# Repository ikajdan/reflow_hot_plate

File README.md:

<h1 align="center">
  
  <br><br>
  Reflow Hot Plate
  <br><br>
</h1>

<p align="center">
  <a href="#features">Features</a> •
  <a href="#hardware">Hardware</a> •
  <a href="#firmware">Firmware</a> •
  <a href="#usage">Usage</a> •
  <a href="#gallery">Gallery</a> •
  <a href="#license">License</a>
</p>

The STM32-Based Reflow Hot Plate Project is an open-source initiative aimed at creating a reflow soldering hot plate using the STM32 microcontroller. This project provides an affordable and customizable solution for hobbyists looking to solder surface-mount components onto printed circuit boards with precision and control.

## Features

- **Precise temperature control:** The STM32 microcontroller provides accurate temperature control, ensuring optimal soldering results for a wide range of solder pastes and components.
- **User-friendly interface:** A user-friendly interface, featuring an OLED display and tactile buttons, allows you to easily set and monitor reflow profiles.
- **Customizable reflow profiles:** Create, edit, and save reflow profiles tailored to your specific soldering requirements.
- **Safety mechanisms:** Built-in safety features, such as over-temperature protection and emergency shut-off, ensure a secure soldering environment.
- **Open-source:** The entire project, including schematics, PCB layouts, and firmware is open-source and available for improvement and customization.

## Hardware

The electronic hardware is designed using KiCad. It includes the following components:

- STM32 microcontroller (STM32F103 series)
- N-Channel Power MOSFET for controlling the heating element
- Thermocouple and PT100 sensor for temperature measurement
- OLED display for real-time temperature and soldering progress information
- Buttons for user interaction
- USB-C connector for communication
- Power supply circuitry

The mechanical hardware is designed using FreeCAD. It includes the following components:

- Front panel mask
- Front panel brackets
- Gooseneck mounting

These components are designed to be 3D printed and assembled together to create a complete device.

For detailed hardware schematics, PCB layout and CAD models, please refer to the [Hardware](hardware/) directory.

## Firmware

The firmware for the reflow hot plate is developed using the STM32CubeIDE. It includes:

- Temperature control algorithm
- User interface logic
- Reflow profile management
- Safety and emergency handling

The Cube project can be found in the [Firmware](firmware/) directory.

## Usage

1. Power on the reflow hot plate and wait for it to initialize.
1. Place your PCB with solder paste and components onto the hot plate.
1. Use the tactile buttons and OLED display to navigate through the user interface and select a reflow profile.
1. The hot plate will execute the selected reflow profile, precisely controlling the temperature to solder the components onto the PCB.
1. Once the reflow process is complete, allow the PCB to cool before removing it from the hot plate.

## Gallery

</img>
</img>
</img>
</img>
</img>
</img>

## License

This project is licensed under the [MIT License](LICENSE.md), which means you are free to use, modify, and distribute the project's source code and documentation for both commercial and non-commercial purposes.

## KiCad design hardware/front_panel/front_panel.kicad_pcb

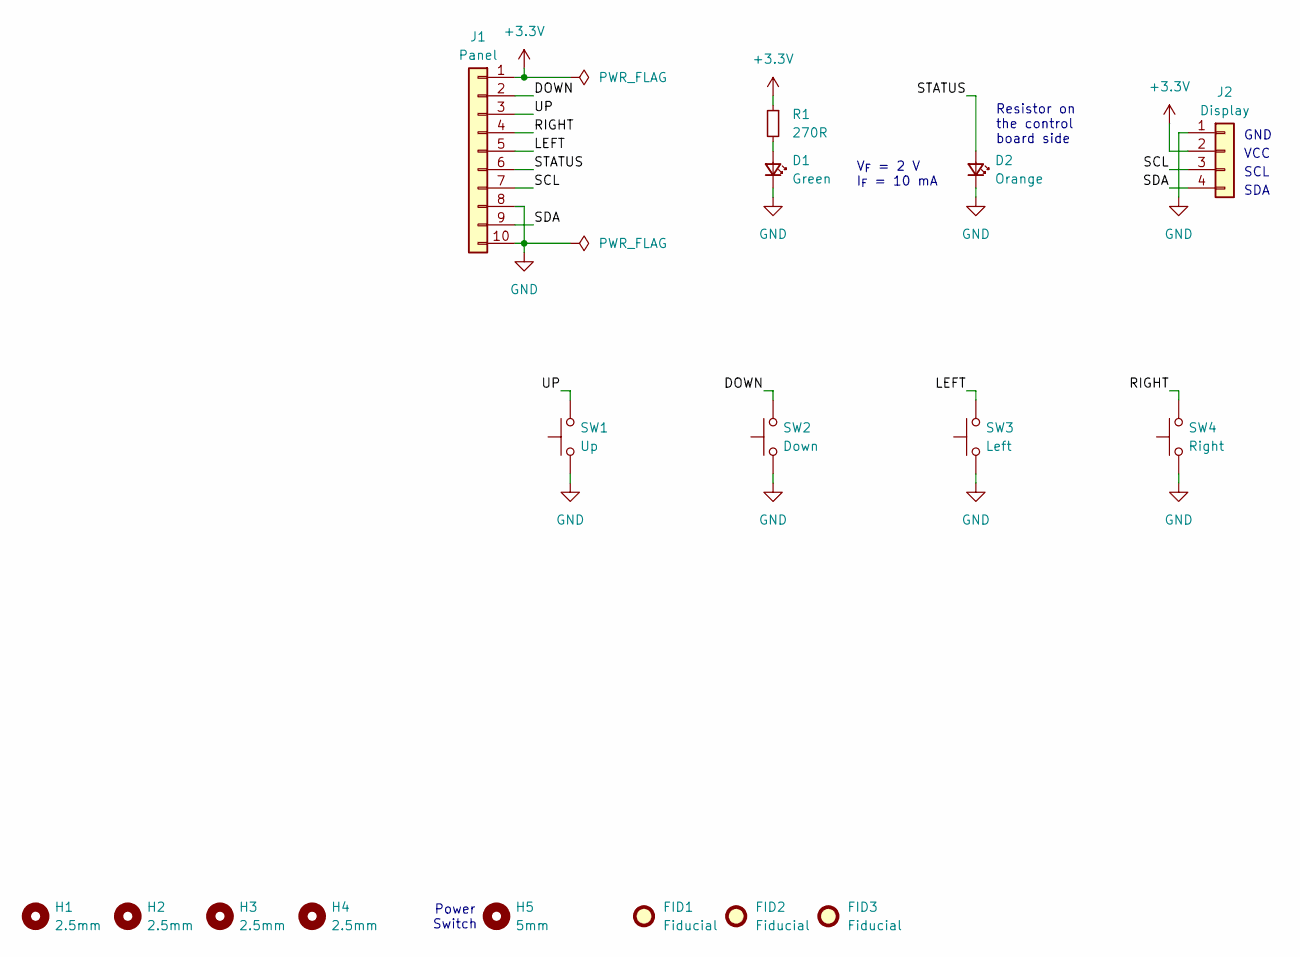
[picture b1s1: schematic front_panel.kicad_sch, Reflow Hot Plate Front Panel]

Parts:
D1: Green; LED_D3.0mm_FlatTop
D2: Orange; LED_D3.0mm_FlatTop
FID1, FID2, FID3: Fiducial; Fiducial_1mm_Mask2mm
H1, H2, H3, H4: 2.5mm; MountingHole_2.5mm
H5: 5mm; MountingHole_5mm
J1: Panel; 52808-1070
J2: Display; 0.96_OLED
R1: 270R; R_0603_1608Metric
SW1: Up; SW_PUSH_6mm_H7.3mm
SW2: Down; SW_PUSH_6mm_H7.3mm
SW3: Left; SW_PUSH_6mm_H7.3mm
SW4: Right; SW_PUSH_6mm_H7.3mm

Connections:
+3.3V: J1.1, J2.2, R1.1
/DOWN: J1.2, SW2.2
/LEFT: J1.5, SW3.2
/RIGHT: J1.4, SW4.2
/SCL: J1.7, J2.3
/SDA: J1.9, J2.4
/STATUS: D2.2 (A), J1.6
/UP: J1.3, SW1.2
GND: D1.1 (K), D2.1 (K), J1.8, J1.10, J2.1, SW1.1, SW2.1, SW3.1, SW4.1
unnamed: D1.2 (A), R1.2

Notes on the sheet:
Resistor on the control board side
Power Switch
SCL
GND
SDA
VCC
V_{F} = 2 V I_{F} = 10 mA

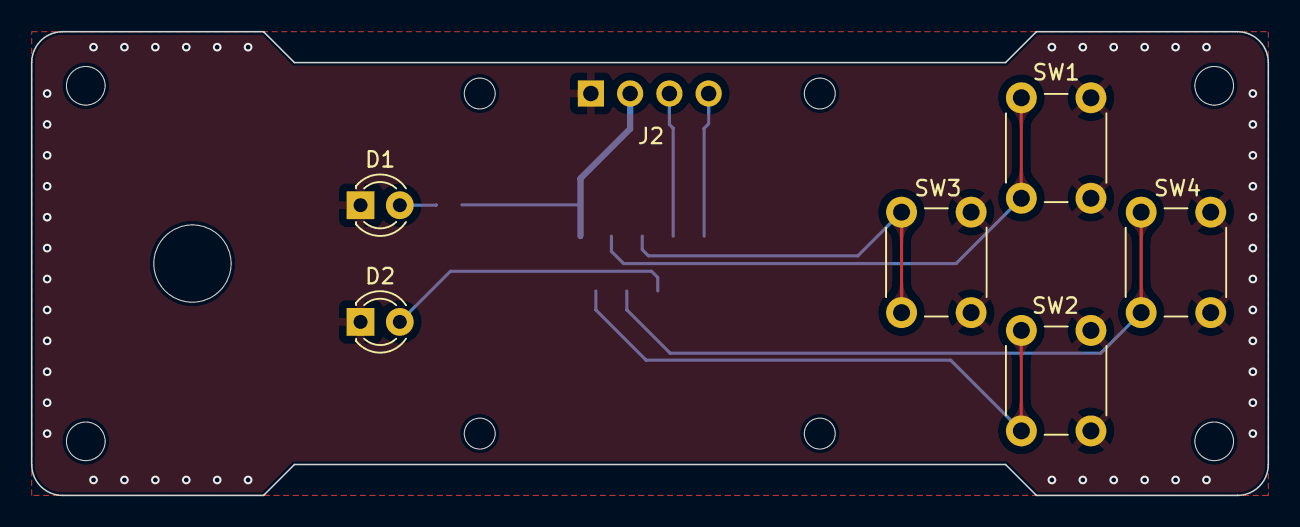
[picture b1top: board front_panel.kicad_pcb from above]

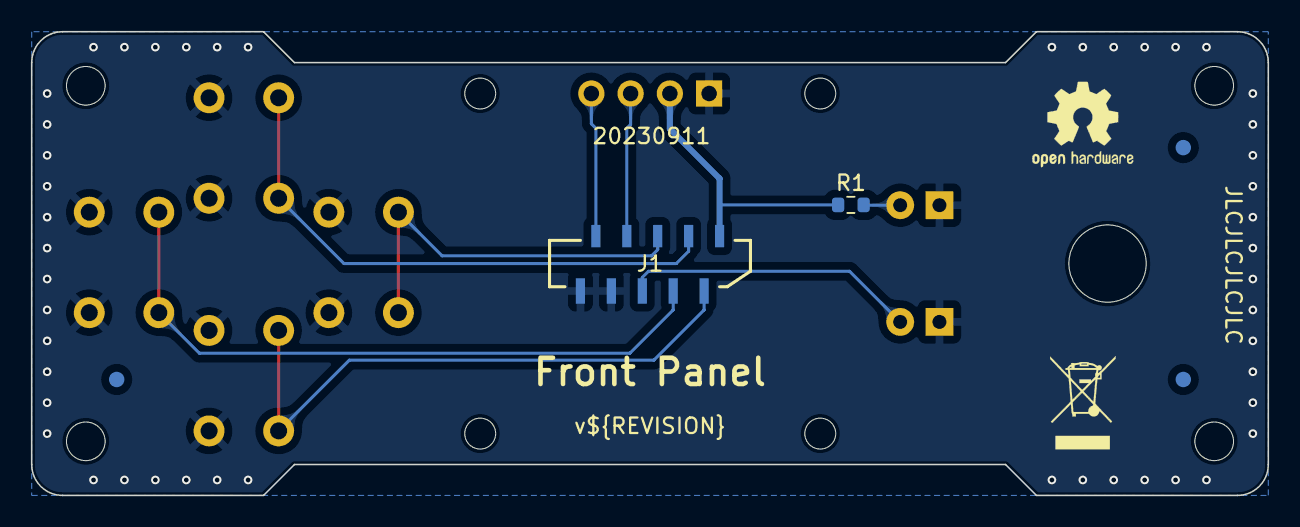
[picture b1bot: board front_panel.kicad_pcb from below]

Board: 2 copper layers, 80.0 x 30.0 mm, 17 parts (5 on the bottom side), 10 nets.

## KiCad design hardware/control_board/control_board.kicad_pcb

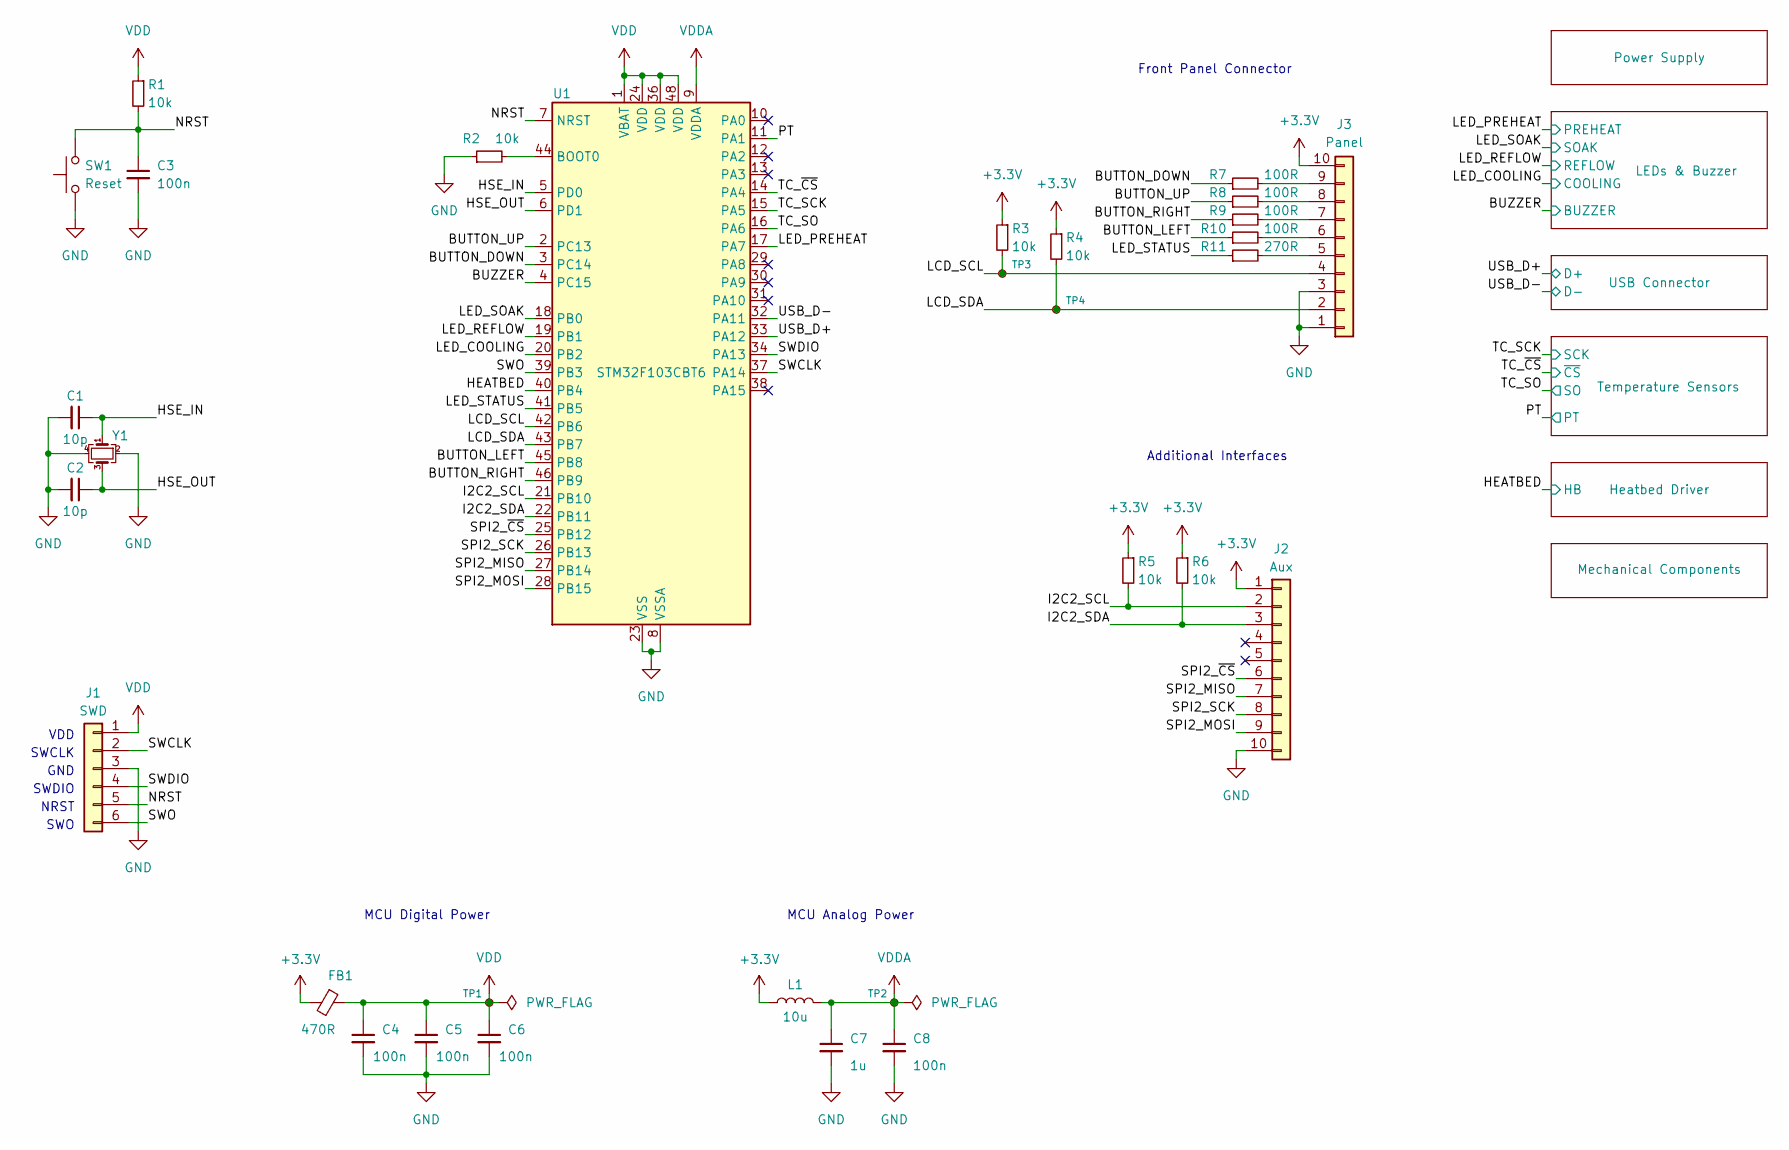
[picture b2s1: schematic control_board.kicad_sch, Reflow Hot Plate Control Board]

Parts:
C1, C2: 10p; C_0603_1608Metric
C3, C4, C5, C6, C8: 100n; C_0603_1608Metric
C7: 1u; C_0603_1608Metric
FB1: 470R; L_0603_1608Metric
J1: SWD; PinHeader_1x06_P2.54mm_Vertical
J2: Aux; PinHeader_2x05_P2.54mm_Vertical
J3: Panel; 52808-1070
L1: 10u; L_0603_1608Metric
R1, R2, R3, R4, R5, R6: 10k; R_0603_1608Metric
R7, R8, R9, R10: 100R; R_0603_1608Metric
R11: 270R; R_0603_1608Metric
SW1: Reset; SW_SPST_B3U-1000P
TP1, TP2, TP3, TP4: TestPoint_Small; TestPoint_Pad_D1.0mm
U1: STM32F103CBT6; LQFP-48_7x7mm_P0.5mm
Y1: 8MHz; Crystal_SMD_3225-4Pin_3.2x2.5mm

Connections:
+3.3V: FB1.2, J2.1, J3.10, L1.1, R3.1, R4.1, R5.1, R6.1; also elsewhere on the board
/BUTTON_DOWN: R7.1, U1.3 (PC14)
/BUTTON_LEFT: R10.1, U1.45 (PB8)
/BUTTON_RIGHT: R9.1, U1.46 (PB9)
/BUTTON_UP: R8.1, U1.2 (PC13)
/BUZZER: U1.4 (PC15); also elsewhere on the board
/HEATBED: U1.40 (PB4); also elsewhere on the board
/HSE_IN: C1.1, U1.5 (PD0), Y1.1
/HSE_OUT: C2.1, U1.6 (PD1), Y1.3
/I2C2_SCL: J2.2, R5.2, U1.21 (PB10)
/I2C2_SDA: J2.3, R6.2, U1.22 (PB11)
/LCD_SCL: J3.4, R3.2, TP3.1, U1.42 (PB6)
/LCD_SDA: J3.2, R4.2, TP4.1, U1.43 (PB7)
/LED_COOLING: U1.20 (PB2); also elsewhere on the board
/LED_PREHEAT: U1.17 (PA7); also elsewhere on the board
/LED_REFLOW: U1.19 (PB1); also elsewhere on the board
/LED_SOAK: U1.18 (PB0); also elsewhere on the board
/LED_STATUS: R11.1, U1.41 (PB5)
/NRST: C3.1, J1.5, R1.2, SW1.2, U1.7 (NRST)
/PT: U1.11 (PA1); also elsewhere on the board
/SPI2_MISO: J2.7, U1.27 (PB14)
/SPI2_MOSI: J2.9, U1.28 (PB15)
/SPI2_SCK: J2.8, U1.26 (PB13)
/SPI2_~CS: J2.6, U1.25 (PB12)
/SWCLK: J1.2, U1.37 (PA14)
/SWDIO: J1.4, U1.34 (PA13)
/SWO: J1.6, U1.39 (PB3)
/TC_SCK: U1.15 (PA5); also elsewhere on the board
/TC_SO: U1.16 (PA6); also elsewhere on the board
/TC_~CS: U1.14 (PA4); also elsewhere on the board
/USB_D+: U1.33 (PA12); also elsewhere on the board
/USB_D-: U1.32 (PA11); also elsewhere on the board
GND: C1.2, C2.2, C3.2, C4.2, C5.2, C6.2, C7.2, C8.2, J1.3, J2.10, J3.1, J3.3, R2.1, SW1.1, U1.8 (VSSA), U1.23 (VSS), U1.35 (VSS), U1.47 (VSS), Y1.2, Y1.4; also elsewhere on the board
unnamed: J3.5, R11.2
unnamed: J3.6, R10.2
unnamed: J3.7, R9.2
unnamed: J3.8, R8.2
unnamed: J3.9, R7.2
unnamed: R2.2, U1.44 (BOOT0)
VDD: C4.1, C5.1, C6.1, FB1.1, J1.1, R1.1, TP1.1, U1.1 (VBAT), U1.24 (VDD), U1.36 (VDD), U1.48 (VDD); also elsewhere on the board
VDDA: C7.1, C8.1, L1.2, TP2.1, U1.9 (VDDA)

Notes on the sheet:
MCU Analog Power
MCU Digital Power
Additional Interfaces
VDD
SWO
SWCLK
Front Panel Connector
SWDIO
NRST
GND

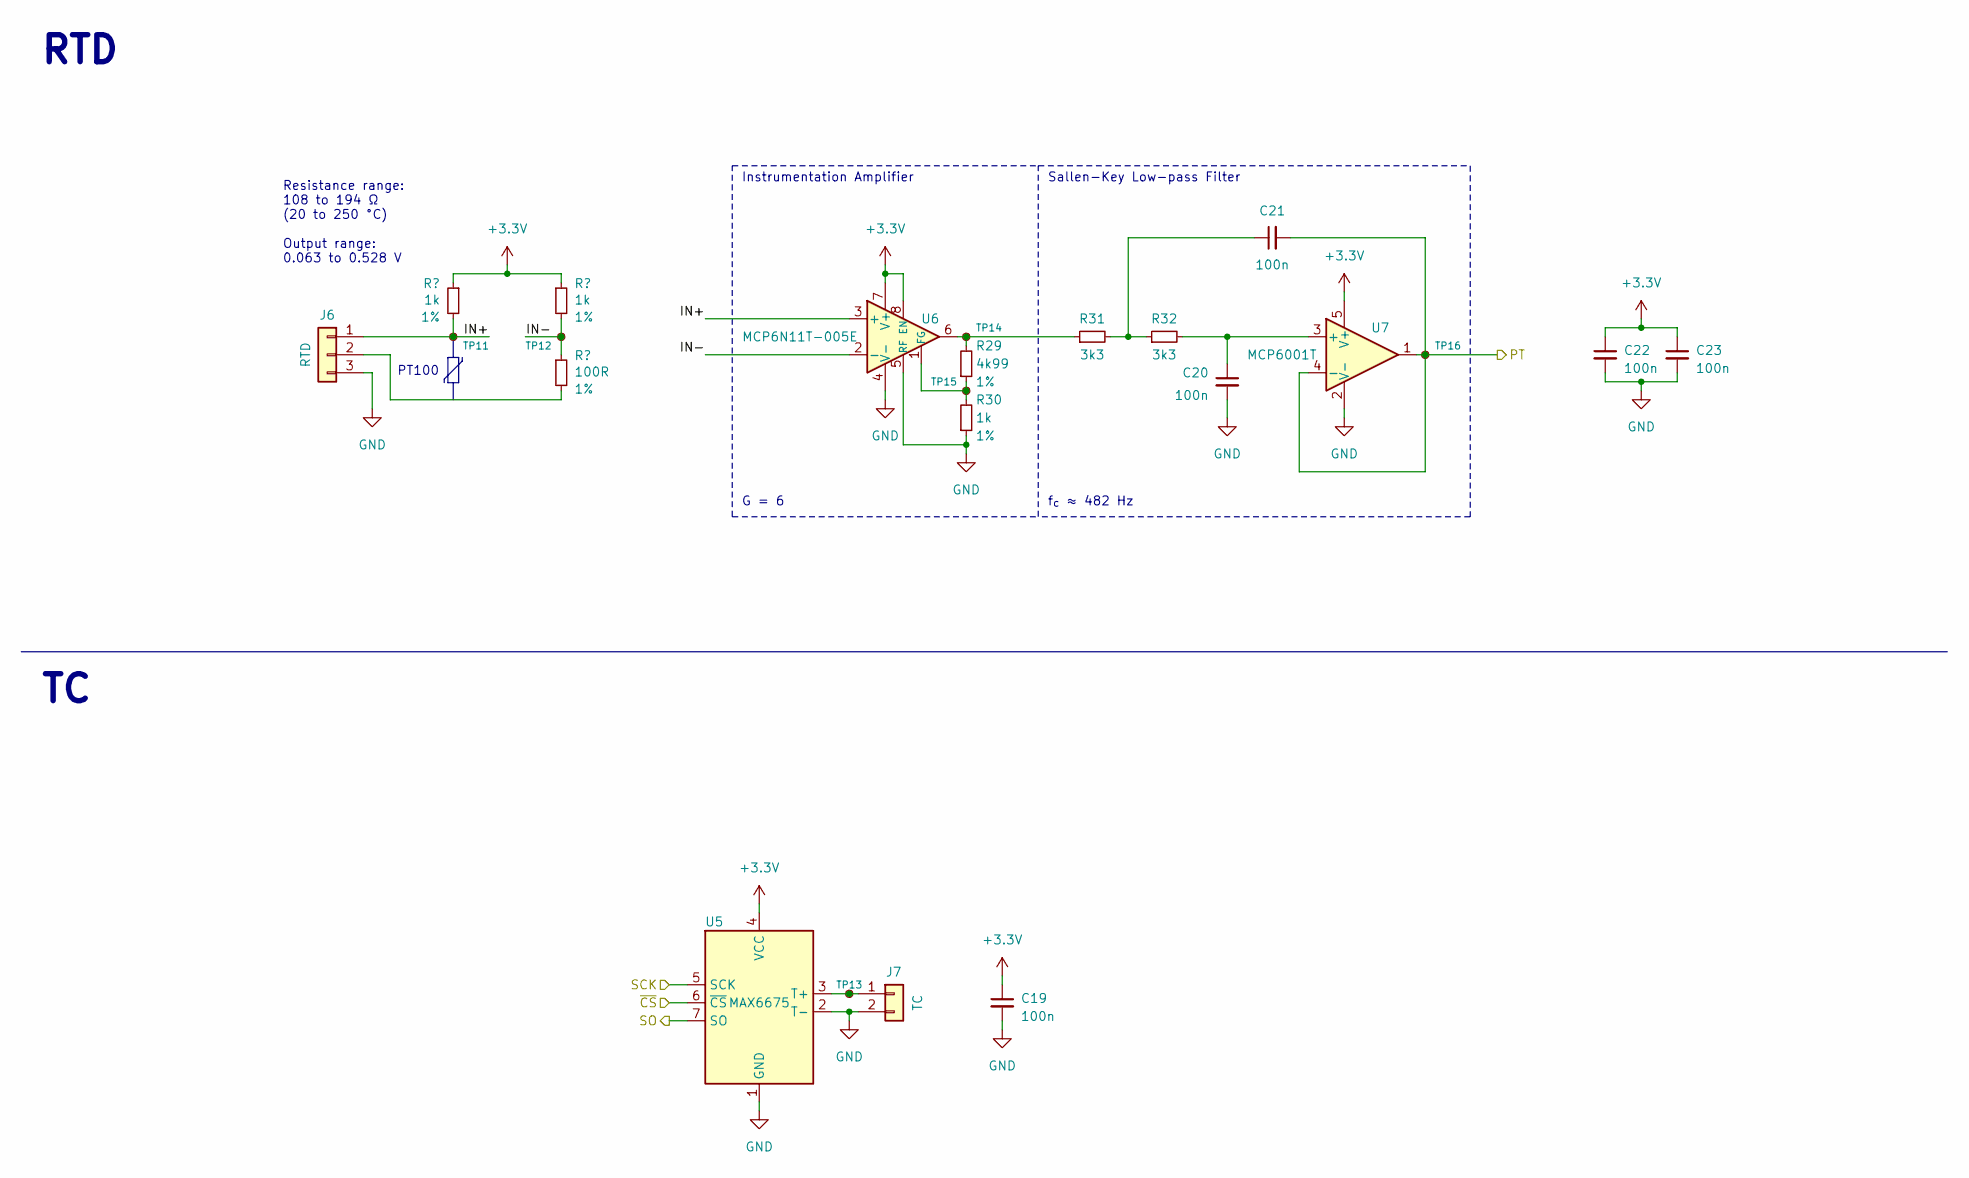
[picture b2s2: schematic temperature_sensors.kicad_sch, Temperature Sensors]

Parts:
C19, C20, C21, C22, C23: 100n; C_0603_1608Metric
J6: RTD; JST_XH_B3B-XH-A_1x03_P2.50mm_Vertical
J7: TC; JST_XH_B2B-XH-A_1x02_P2.50mm_Vertical
R26, R27, R30: 1k; R_0603_1608Metric; Tolerance 1%
R28: 100R; R_0603_1608Metric; Tolerance 1%
R29: 4k99; R_0603_1608Metric; Tolerance 1%
R31, R32: 3k3; R_0603_1608Metric
TP11, TP12, TP13, TP14, TP15, TP16: TestPoint_Small; TestPoint_Pad_D1.0mm
U5: MAX6675; SOIC-8_3.9x4.9mm_P1.27mm
U6: MCP6N11T-005E; SOIC-8_3.9x4.9mm_P1.27mm
U7: MCP6001T; SOT-23-5

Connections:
+3.3V: C19.1, C22.1, C23.1, R26.1, R27.1, U5.4 (VCC), U6.7 (V+), U6.8 (EN), U7.5 (V+); also elsewhere on the board
/PT: C21.2, TP16.1, U7.1, U7.4 (-); also elsewhere on the board
/TC_SCK: U5.5 (SCK); also elsewhere on the board
/TC_SO: U5.7 (SO); also elsewhere on the board
/TC_~CS: U5.6 (~CS); also elsewhere on the board
/Temperature Sensors/IN+: J6.1, R26.2, TP11.1, U6.3 (+)
/Temperature Sensors/IN-: R27.2, R28.1, TP12.1, U6.2 (-)
GND: C19.2, C20.2, C22.2, C23.2, J6.3, J7.2, R30.1, U5.1 (GND), U5.2 (T-), U6.4 (V-), U6.5 (RF), U7.2 (V-); also elsewhere on the board
unnamed: C21.1, R31.2, R32.1
unnamed: J6.2, R28.2
unnamed: J7.1, TP13.1, U5.3 (T+)
unnamed: R29.2, R31.1, TP14.1, U6.6
unnamed: R29.1, R30.2, TP15.1, U6.1 (FG)
unnamed: C20.1, R32.2, U7.3 (+)

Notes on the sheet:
Instrumentation Amplifier
Resistance range: 108 to 194 Ω (20 to 250 °C) Output range: 0.063 to 0.528 V
G = 6
RTD
Sallen-Key Low-pass Filter
f_{c} ≈ 482 Hz
PT100

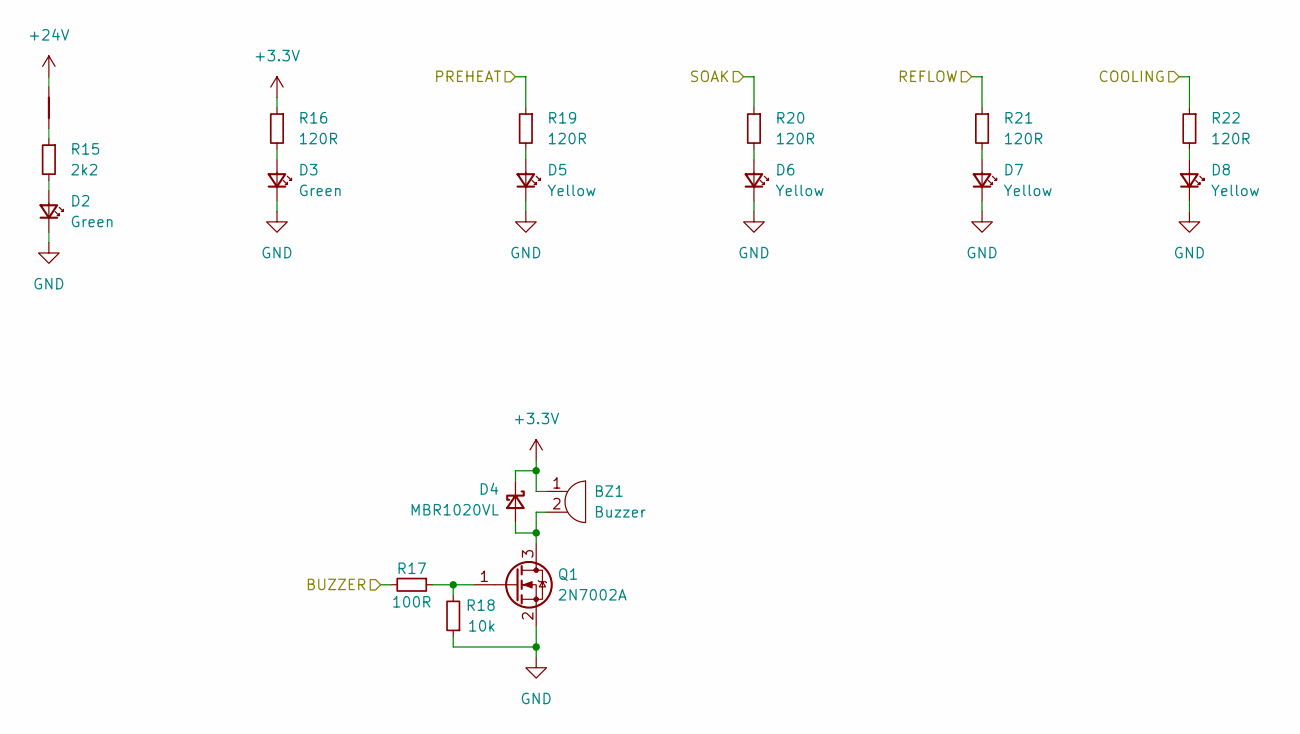
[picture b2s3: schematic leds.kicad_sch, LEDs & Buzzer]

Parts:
BZ1: Buzzer; CMI-9605IC-0380T
D2, D3: Green; LED_0603_1608Metric
D4: MBR1020VL; D_SOD-123F
D5, D6, D7, D8: Yellow; LED_0603_1608Metric
NT1: NetTie_2; NetTie-2_SMD_Pad0.2mm
Q1: 2N7002A; SOT-23
R15: 2k2; R_0603_1608Metric
R16, R19, R20, R21, R22: 120R; R_0603_1608Metric
R17: 100R; R_0603_1608Metric
R18: 10k; R_0603_1608Metric

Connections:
+3.3V: BZ1.1, D4.1 (K), R16.1; also elsewhere on the board
+24V: NT1.2; also elsewhere on the board
/BUZZER: R17.2; also elsewhere on the board
/LED_COOLING: R22.1; also elsewhere on the board
/LED_PREHEAT: R19.1; also elsewhere on the board
/LED_REFLOW: R21.1; also elsewhere on the board
/LED_SOAK: R20.1; also elsewhere on the board
GND: D2.1 (K), D3.1 (K), D5.1 (K), D6.1 (K), D7.1 (K), D8.1 (K), Q1.2 (S), R18.1; also elsewhere on the board
unnamed: D2.2 (A), R15.2
unnamed: D3.2 (A), R16.2
unnamed: BZ1.2, D4.2 (A), Q1.3 (D)
unnamed: D5.2 (A), R19.2
unnamed: D6.2 (A), R20.2
unnamed: D7.2 (A), R21.2
unnamed: D8.2 (A), R22.2
unnamed: NT1.1, R15.1
unnamed: Q1.1 (G), R17.1, R18.2

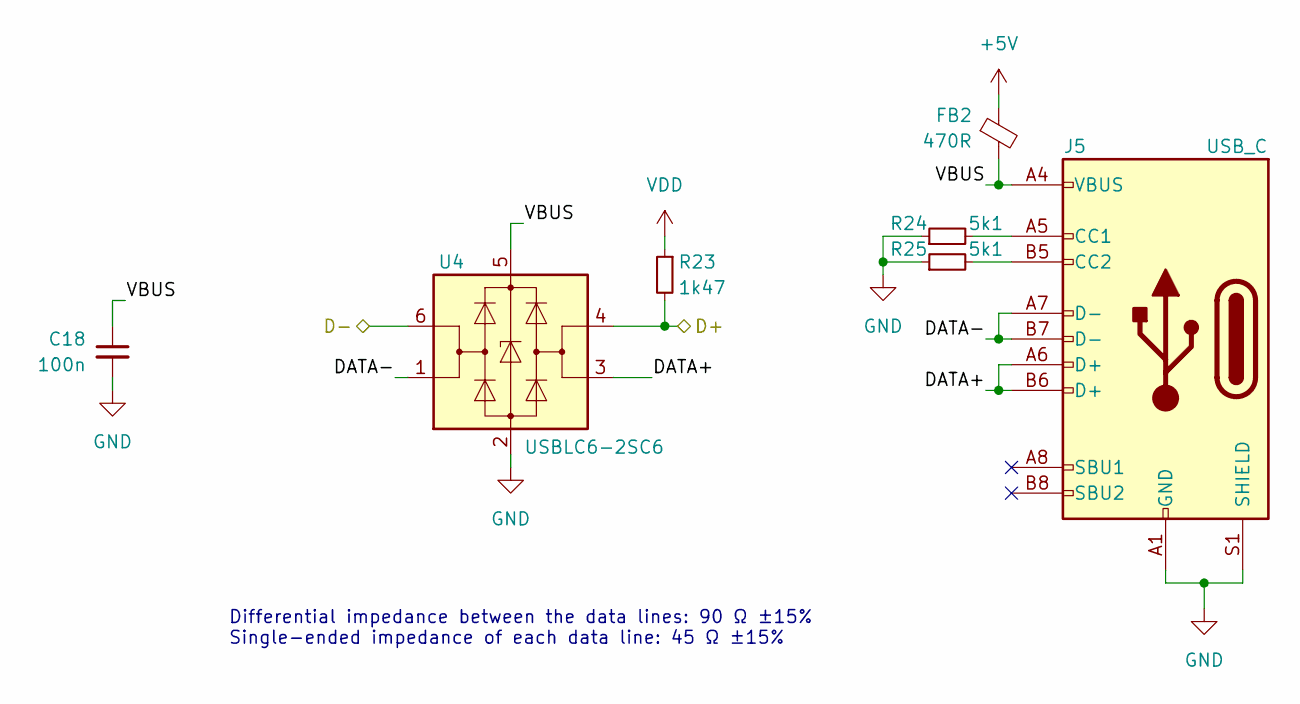
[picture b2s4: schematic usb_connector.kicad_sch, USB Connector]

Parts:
C18: 100n; C_0603_1608Metric
FB2: 470R; L_0603_1608Metric
J5: USB_C; USB4105-GF-A
R23: 1k47; R_0603_1608Metric
R24, R25: 5k1; R_0603_1608Metric
U4: USBLC6-2SC6; SOT-23-6

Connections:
+5V: FB2.1; also elsewhere on the board
/USB Connector/DATA+: J5.A6 (D+), J5.B6 (D+), U4.3 (I/O2)
/USB Connector/DATA-: J5.A7 (D-), J5.B7 (D-), U4.1 (I/O1)
/USB Connector/VBUS: C18.1, FB2.2, J5.A4 (VBUS), J5.A9 (VBUS), J5.B4 (VBUS), J5.B9 (VBUS), U4.5 (VBUS)
/USB_D+: R23.2, U4.4 (I/O2); also elsewhere on the board
/USB_D-: U4.6 (I/O1); also elsewhere on the board
GND: C18.2, J5.A1 (GND), J5.A12 (GND), J5.B1 (GND), J5.B12 (GND), J5.S1 (SHIELD), R24.1, R25.1, U4.2 (GND); also elsewhere on the board
unnamed: J5.A5 (CC1), R24.2
unnamed: J5.B5 (CC2), R25.2
VDD: R23.1; also elsewhere on the board

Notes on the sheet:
Differential impedance between the data lines: 90 Ω ±15% Single-ended impedance of each data line: 45 Ω ±15%

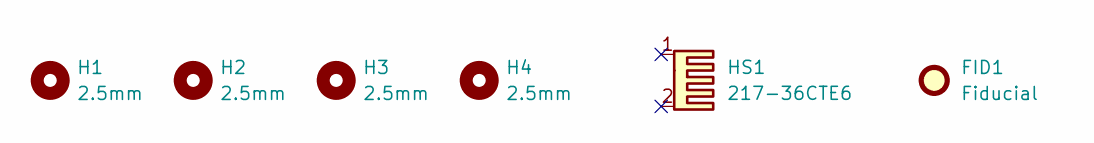
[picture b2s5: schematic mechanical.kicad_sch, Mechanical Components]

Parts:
FID1: Fiducial; Fiducial_1mm_Mask2mm
H1, H2, H3, H4: 2.5mm; MountingHole_2.5mm
HS1: 217-36CTE6; 217-36CTx6

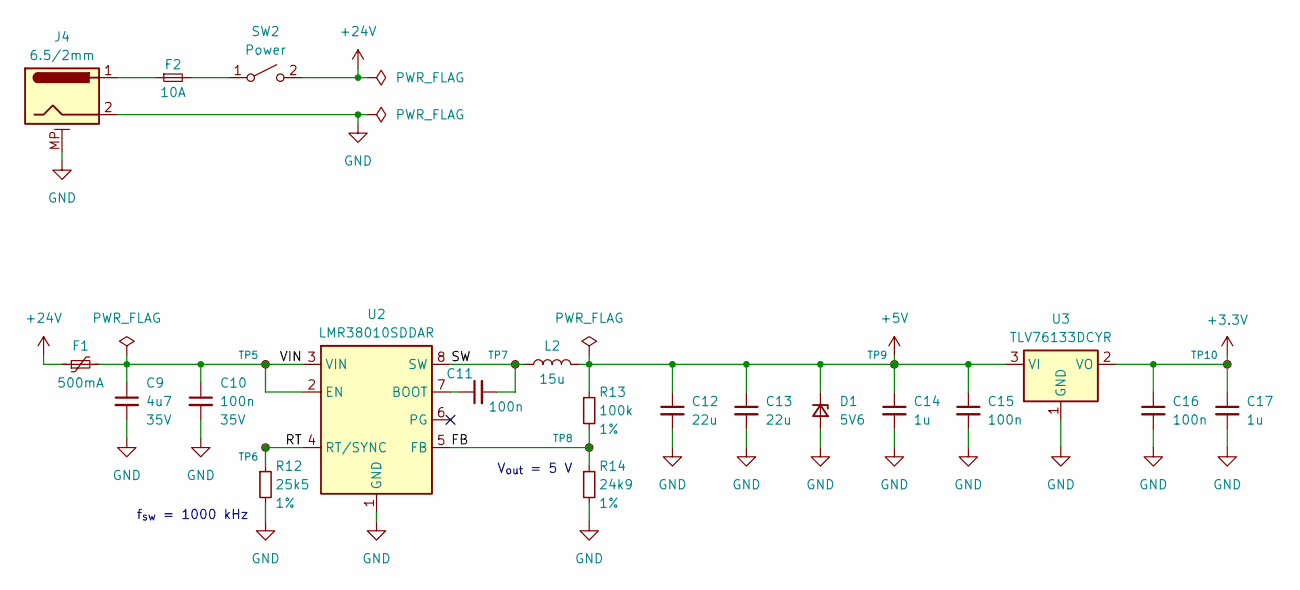
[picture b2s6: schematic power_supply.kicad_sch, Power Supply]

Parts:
C9: 4u7; C_0603_1608Metric; Rated Voltage 35V
C10: 100n; C_0603_1608Metric; Rated Voltage 35V
C11, C15, C16: 100n; C_0603_1608Metric
C12, C13: 22u; C_0603_1608Metric
C14, C17: 1u; C_0603_1608Metric
D1: 5V6; D_SOD-123F
F1: 500mA; MINISMDCx
F2: 10A; Fuseholder_Cylinder-5x20mm_Schurter_0031_8201_Horizontal_Op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
J4: 6.5/2mm; BarrelJack_CUI_PJ-063AH_Horizontal
L2: 15u; SRN6028Cx
R12: 25k5; R_0603_1608Metric; Tolerance 1%
R13: 100k; R_0603_1608Metric; Tolerance 1%
R14: 24k9; R_0603_1608Metric; Tolerance 1%
SW2: Power; SwitchWireRelief
TP5, TP6, TP7, TP8, TP9, TP10: TestPoint_Small; TestPoint_Pad_D1.0mm
U2: LMR38010SDDAR; TI_SO-PowerPAD-8_ThermalVias
U3: TLV76133DCYR; SOT-223-3_TabPin2

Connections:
+3.3V: C16.1, C17.1, TP10.1, U3.2 (VO); also elsewhere on the board
+5V: C12.1, C13.1, C14.1, C15.1, D1.1 (K), L2.2, R13.1, TP9.1, U3.3 (VI); also elsewhere on the board
+24V: F1.1, SW2.2 (B); also elsewhere on the board
/Power Supply/FB: R13.2, R14.1, TP8.1, U2.5 (FB)
/Power Supply/RT: R12.1, TP6.1, U2.4 (RT/SYNC)
/Power Supply/SW: C11.2, L2.1, TP7.1, U2.8 (SW)
/Power Supply/VIN: C9.1, C10.1, F1.2, TP5.1, U2.2 (EN), U2.3 (VIN)
GND: C9.2, C10.2, C12.2, C13.2, C14.2, C15.2, C16.2, C17.2, D1.2 (A), J4.2, J4.MP (MountPin), R12.2, R14.2, U2.1 (GND), U2.9 (EP), U3.1 (GND); also elsewhere on the board
unnamed: F2.1, J4.1
unnamed: F2.2, SW2.1 (A)
unnamed: C11.1, U2.7 (BOOT)

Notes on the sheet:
f_{sw} = 1000 kHz
V_{out} = 5 V

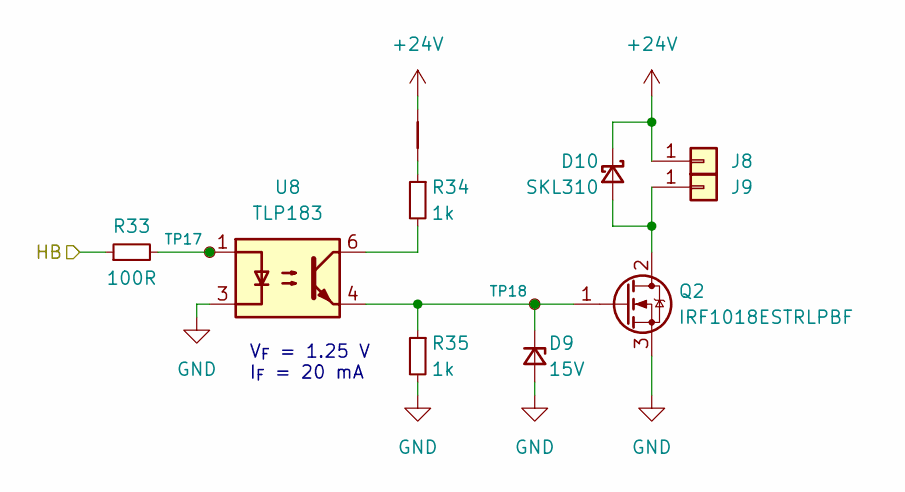
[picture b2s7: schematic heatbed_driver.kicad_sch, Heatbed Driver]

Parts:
D9: 15V; D_SOD-123F
D10: SKL310; D_SOD-123F
J8, J9: Conn_01x01; Pad_D5mm_H2.2mm_Via
NT2: NetTie_2; NetTie-2_SMD_Pad0.2mm
Q2: IRF1018ESTRLPBF; TO-263-2
R33: 100R; R_0603_1608Metric
R34, R35: 1k; R_0603_1608Metric
TP17, TP18: TestPoint_Small; TestPoint_Pad_D1.0mm
U8: TLP183; SOIC-4_4.55x3.7mm_P2.54mm

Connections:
+24V: D10.1 (K), J8.1, NT2.2; also elsewhere on the board
/HEATBED: R33.1; also elsewhere on the board
GND: D9.2 (A), Q2.3 (S), R35.2, U8.3; also elsewhere on the board
unnamed: D9.1 (K), Q2.1 (G), R35.1, TP18.1, U8.4
unnamed: D10.2 (A), J9.1, Q2.2 (D)
unnamed: NT2.1, R34.1
unnamed: R33.2, TP17.1, U8.1
unnamed: R34.2, U8.6

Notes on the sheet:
V_{F} = 1.25 V I_{F} = 20 mA

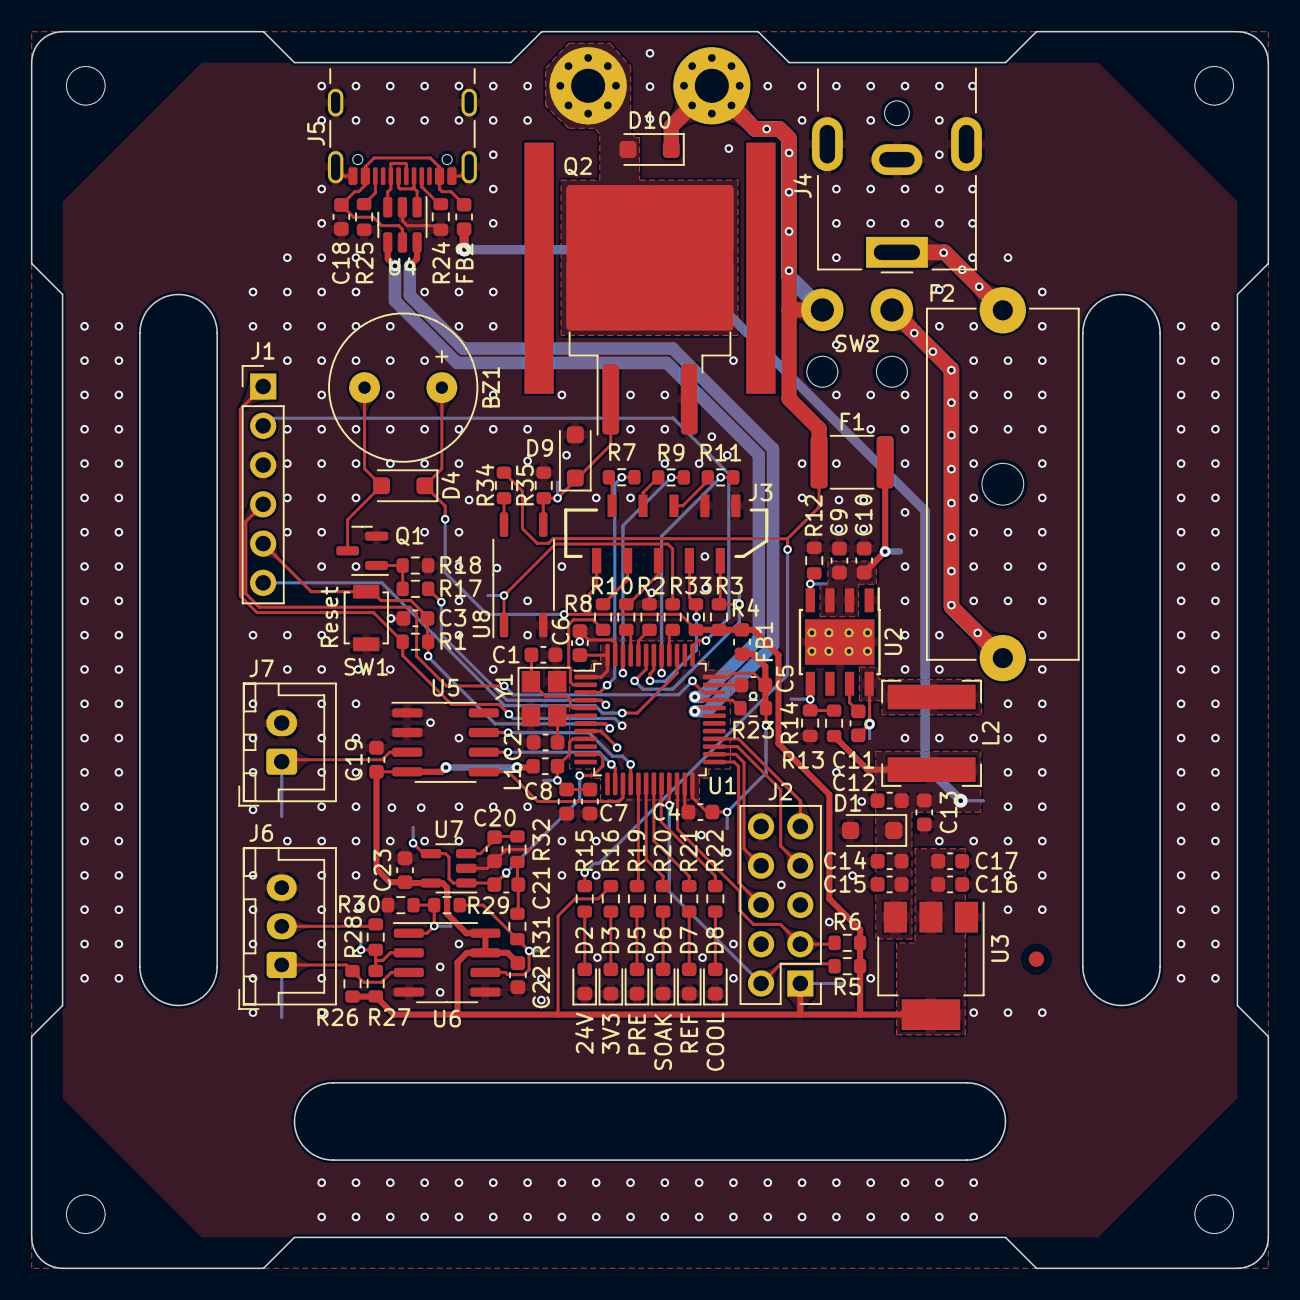
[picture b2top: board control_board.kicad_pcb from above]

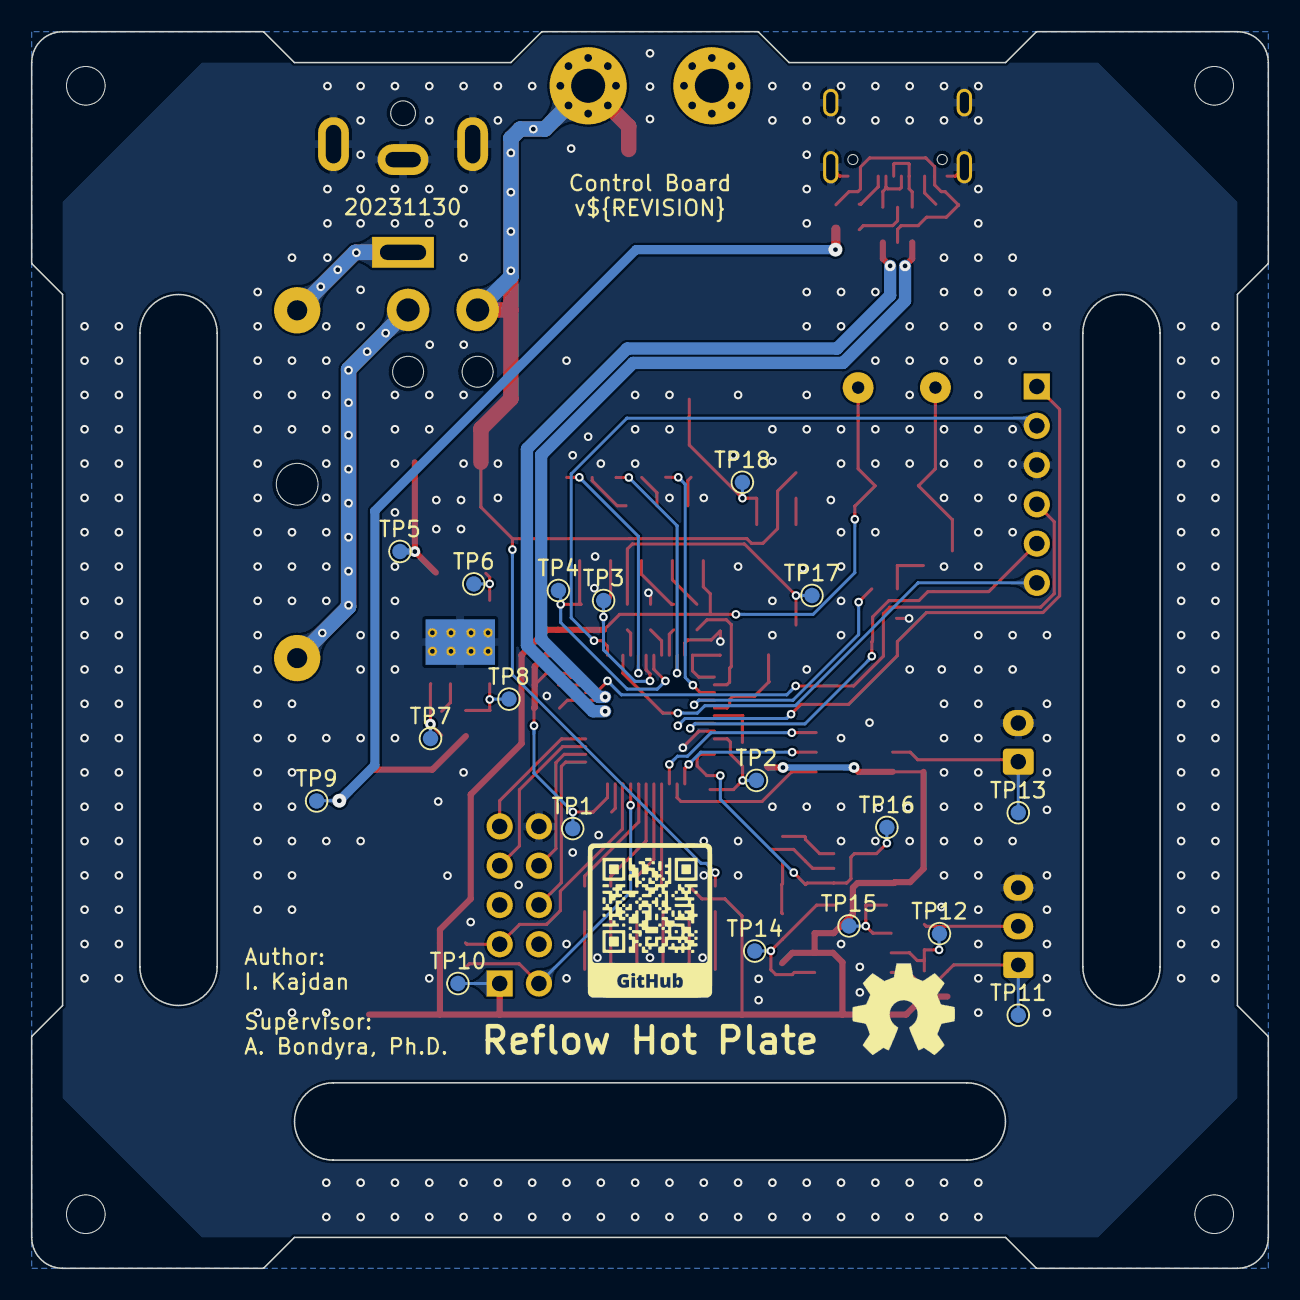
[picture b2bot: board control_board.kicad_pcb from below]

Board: 2 copper layers, 80.0 x 80.0 mm, 123 parts (18 on the bottom side), 77 nets.

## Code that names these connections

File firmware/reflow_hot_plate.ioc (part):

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Mcu.Name=STM32F103C(8-B)Tx
Mcu.Package=LQFP48
Mcu.UserName=STM32F103CBTx
PA1.GPIOParameters=GPIO_Label
PA1.GPIO_Label=PT
PA1.Signal=ADCx_IN1
PA11.GPIOParameters=GPIO_Label
PA11.GPIO_Label=USB_D-
PA11.Mode=Device
PA11.Signal=USB_DM
PA12.GPIOParameters=GPIO_Label
PA12.GPIO_Label=USB_D+
PA12.Mode=Device
PA12.Signal=USB_DP
PA13.GPIOParameters=GPIO_Label
PA13.GPIO_Label=SWDIO
PA13.Mode=Trace_Asynchronous_SW
PA13.Signal=SYS_JTMS-SWDIO
PA14.GPIOParameters=GPIO_Label
PA14.GPIO_Label=SWCLK
PA14.Mode=Trace_Asynchronous_SW
PA14.Signal=SYS_JTCK-SWCLK
PA4.GPIOParameters=GPIO_Label
PA4.GPIO_Label=TC_CS
PA4.Signal=GPIO_Output
PA5.GPIOParameters=GPIO_Label
PA5.GPIO_Label=TC_SCK
PA5.Mode=RX_Only_Simplex_Unidirect_Master
PA5.Signal=SPI1_SCK
PA6.GPIOParameters=GPIO_Label
PA6.GPIO_Label=TC_SO
PA6.Mode=RX_Only_Simplex_Unidirect_Master
PA6.Signal=SPI1_MISO
PA7.GPIOParameters=GPIO_Label
PA7.GPIO_Label=LED_PREHEAT
PA7.Signal=GPIO_Output
PB0.GPIOParameters=GPIO_Label
PB0.GPIO_Label=LED_SOAK
PB0.Signal=GPIO_Output
PB1.GPIOParameters=GPIO_Label
PB1.GPIO_Label=LED_REFLOW
PB1.Signal=GPIO_Output
PB10.Mode=I2C
PB10.Signal=I2C2_SCL
PB11.Mode=I2C
PB11.Signal=I2C2_SDA
PB12.GPIOParameters=GPIO_Label
PB12.GPIO_Label=SPI2_CS
PB12.Signal=GPIO_Output
PB13.Mode=Full_Duplex_Master
PB13.Signal=SPI2_SCK
PB14.Mode=Full_Duplex_Master
PB14.Signal=SPI2_MISO
PB15.Mode=Full_Duplex_Master
PB15.Signal=SPI2_MOSI
PB2.GPIOParameters=GPIO_Label
PB2.GPIO_Label=LED_COOLING
PB2.Signal=GPIO_Output
PB3.GPIOParameters=GPIO_Label
PB3.GPIO_Label=SWO
PB3.Mode=Trace_Asynchronous_SW
PB3.Signal=SYS_JTDO-TRACESWO
PB4.GPIOParameters=GPIO_Label
PB4.GPIO_Label=HEATBED
PB4.Signal=S_TIM3_CH1
PB5.GPIOParameters=GPIO_Label
PB5.GPIO_Label=LED_STATUS
PB5.Signal=GPIO_Output
PB6.GPIOParameters=GPIO_Label
PB6.GPIO_Label=LCD_SCL
PB6.Mode=I2C
PB6.Signal=I2C1_SCL
PB7.GPIOParameters=GPIO_Label
PB7.GPIO_Label=LCD_SDA
PB7.Mode=I2C
PB7.Signal=I2C1_SDA
PB8.GPIOParameters=GPIO_PuPd,GPIO_Label
PB8.GPIO_Label=BUTTON_LEFT
PB8.GPIO_PuPd=GPIO_PULLUP
PB8.Signal=GPXTI8
PB9.GPIOParameters=GPIO_PuPd,GPIO_Label
PB9.GPIO_Label=BUTTON_RIGHT
PB9.GPIO_PuPd=GPIO_PULLUP
PB9.Signal=GPXTI9
PC13-TAMPER-RTC.GPIOParameters=GPIO_PuPd,GPIO_Label
PC13-TAMPER-RTC.GPIO_Label=BUTTON_UP
PC13-TAMPER-RTC.GPIO_PuPd=GPIO_PULLUP
PC13-TAMPER-RTC.Signal=GPXTI13
PC14-OSC32_IN.GPIOParameters=GPIO_PuPd,GPIO_Label
PC14-OSC32_IN.GPIO_Label=BUTTON_DOWN
PC14-OSC32_IN.GPIO_PuPd=GPIO_PULLUP
PC14-OSC32_IN.Signal=GPXTI14
PC15-OSC32_OUT.GPIOParameters=GPIO_Label
PC15-OSC32_OUT.GPIO_Label=BUZZER
PC15-OSC32_OUT.Signal=GPIO_Output
PD0-OSC_IN.GPIOParameters=GPIO_Label
PD0-OSC_IN.GPIO_Label=HSE_IN
PD0-OSC_IN.Mode=HSE-External-Oscillator
PD0-OSC_IN.Signal=RCC_OSC_IN
PD1-OSC_OUT.GPIOParameters=GPIO_Label
PD1-OSC_OUT.GPIO_Label=HSE_OUT
PD1-OSC_OUT.Mode=HSE-External-Oscillator
PD1-OSC_OUT.Signal=RCC_OSC_OUT
RCC.SYSCLKFreq_VALUE=72000000
RCC.SYSCLKSource=RCC_SYSCLKSOURCE_PLLCLK
board=custom
